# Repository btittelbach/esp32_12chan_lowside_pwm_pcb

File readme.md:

# esp32_12chan_lowside_pwm_pcb

Open Hardware PCB designed to drive 12 low-side PWM channels.

It's designed to work with e.g. WLED firmware and can drive up to 4 RGB LED strips.

You can however use it for whatever you want.
Free-wheeling diodes were added, in case someone wants to use it to drive bigger inductive loads.

[Schematic](renderings/pcb_esp32_wled_pwm_multichannel.pdf)

## Power

### Input

Power by USB for easy flashing.

Or power via screw-terminal: DC from 4V up to 28V.

#### optional Sound-Reactive Microphone Input

- I2S SD pin: gpio4
- I2S WS pin: gpio14
- I2S SCK pin: gpio13

### Output

The four screw terminals each group VDD as well as 4 GPIO controlled PWM-channels to GND.

- terminal 1: VDD, gpio16, gpio17, gpio18
- terminal 2: VDD, gpio19, gpio21, gpio22
- terminal 3: VDD, gpio23, gpio25, gpio26
- terminal 4: VDD, gpio27, gpio32, gpio33

## Firmware

for easy use, flash WLED-ESP32 and use web-interface to configure
4 "LEDS" as RGB-Strips with GPIO pins listed above.

## Manufacturing

the board was not designed to minimize costs, but for durability.

The folder `esp32_12chan_lowside_pwm_pcb_v3` includes all manufacturing files and information,
so you should easily be able to order your own.

See [fabrication_data.md](esp32_12chan_lowside_pwm_pcb_v3/fabrication_data.md) for specs often asked in order to get a quote.

### Expensive Parts
- the MosFETs
- the choosen ESP32, though you may choose a version with less Flash
- the QFN USB to UART bridge
- the buck regulator

### Costs

big price hike in 2025:

- per PCB the parts cost roughly 23 USD
- production+assembly+parts come to roughly 54 USD per PCB

## License

This project is licensed under the CERN OH License - see the [LICENSE](LICENSE.txt) file for details

## Photos

## Ordering

List of PCB Suppliers which one-click ordering for the board. (so far only one)

- [PCBWay](https://www.pcbway.com/project/shareproject/W18448ASS50_esp32_12chan_wled_pwm_v3_13ab729a.html)

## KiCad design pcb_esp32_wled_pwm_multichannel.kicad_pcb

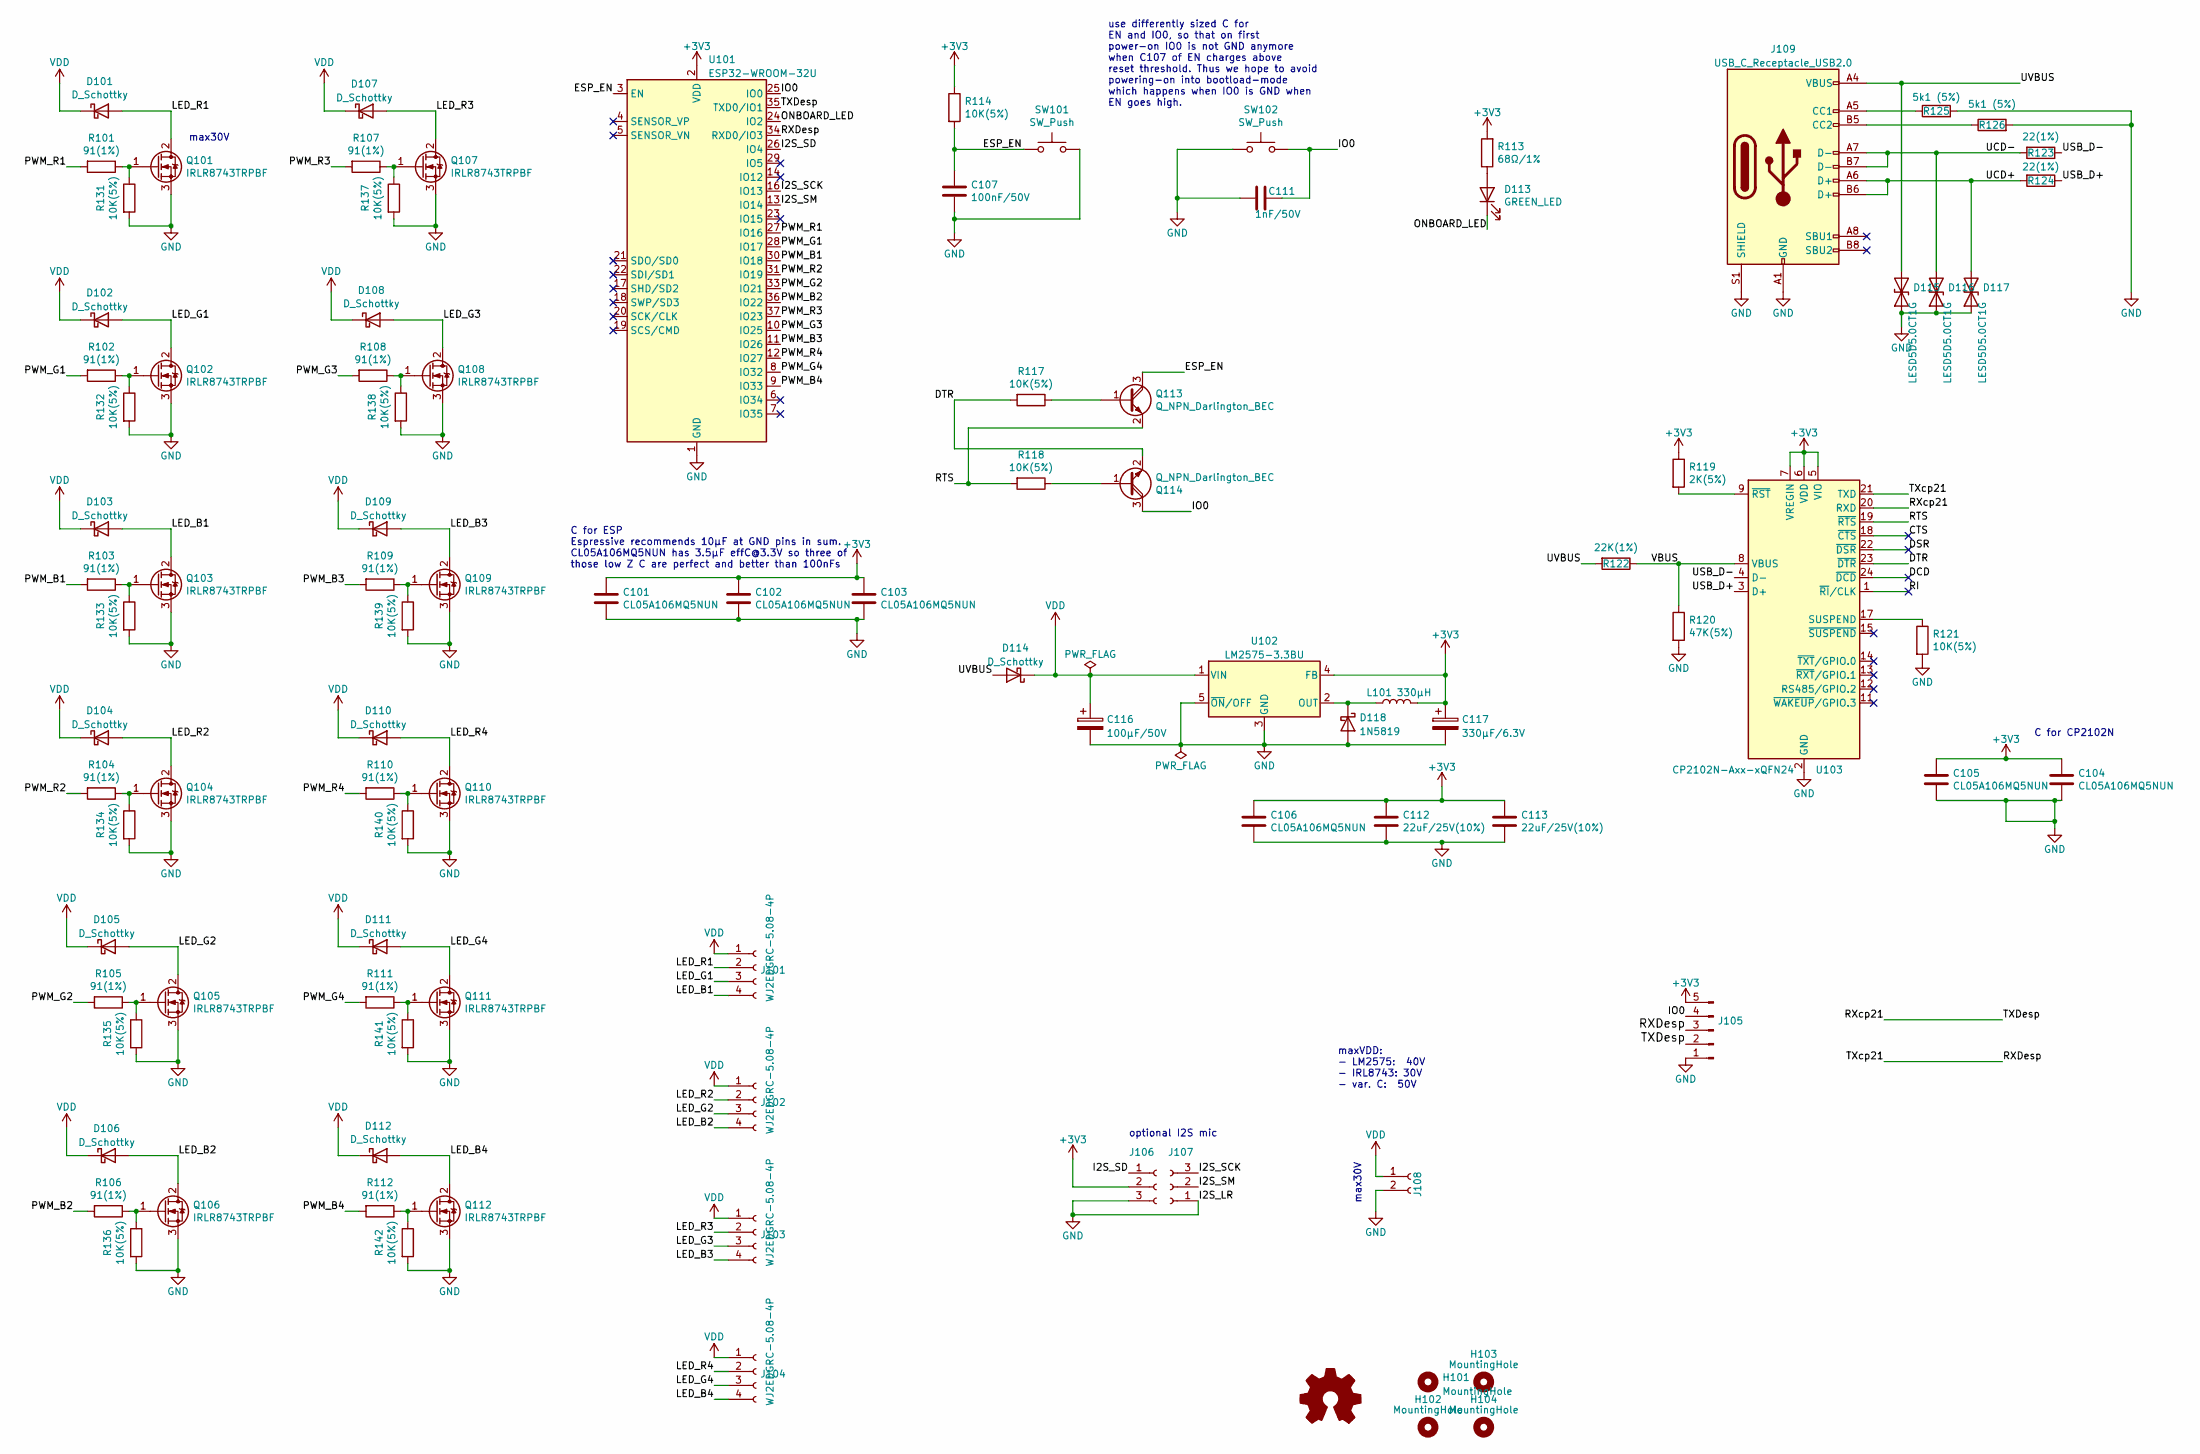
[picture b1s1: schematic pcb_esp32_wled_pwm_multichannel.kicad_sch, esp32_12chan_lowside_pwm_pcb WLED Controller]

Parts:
C101, C102, C103, C104, C105, C106: CL05A106MQ5NUN; C_0402_1005Metric; LCSC C15525
C107: 100nF/50V; C_0603_1608Metric; LCSC C42998
C111: 1nF/50V; C_0603_1608Metric; LCSC C100040
C112, C113: 22uF/25V(10%); C_1210_3225Metric; LCSC C337455
C116: 100µF/50V; CP_Elec_6.3x7.7; LCSC C311622
C117: 330µF/6.3V; CP_Elec_6.3x7.7; LCSC C74623
D101, D102, D103, D104, D105, D106, D107, D108, D109, D110, D111, D112, D114: D_Schottky; D_SOD-123F; LCSC C496544
D113: GREEN_LED; LED_0603_1608Metric; LCSC C89809
D115, D116, D117: LESD5D5.0CT1G; D_SOD-523; LCSC C383211
D118: 1N5819; D_DO-41_SOD81_P10.16mm_Horizontal
H101, H102, H103, H104: MountingHole; MountingHole_3.2mm_M3_ISO7380
J101, J102, J103, J104: WJ2EDGRC-5.08-4P; 2EDGRC-5.08-04P-14-100AH; LCSC C8446
J105: Conn_01x05_Male; PinHeader_1x05_P2.54mm_Vertical
J106, J107: Conn_01x03_Female; PinSocket_1x03_P2.54mm_Vertical; LCSC C358717
J108: Conn_01x02_Female; 2EDGRC-5.08-02P-14-100AH; LCSC C3697
J109: USB_C_Receptacle_USB2.0; USB_C_Receptacle_CIKI_TYPE-C-2.0-16PIN-SMT-3; LCSC C2987386
L101: 330µH; L_12x12mm_H8mm; LCSC C2929508
Q101, Q102, Q103, Q104, Q105, Q106, Q107, Q108, Q109, Q110, Q111, Q112: IRLR8743TRPBF; TO-252-2; LCSC C3040285
Q113, Q114: Q_NPN_Darlington_BEC; SOT-23; LCSC C164885
R101, R102, R103, R104, R105, R106, R107, R108, R109, R110, R111, R112: 91(1%); R_0603_1608Metric
R113: 68Ω/1%; R_0603_1608Metric; LCSC C126362
R114, R117, R118, R121, R131, R132, R133, R134, R135, R136, R137, R138, R139, R140, R141, R142: 10K(5%); R_0603_1608Metric
R119: 2K(5%); R_0603_1608Metric
R120: 47K(5%); R_0603_1608Metric
R122: 22K(1%); R_0603_1608Metric
R123, R124: 22(1%); R_0603_1608Metric
R125, R126: 5k1 (5%); R_0603_1608Metric
SW101, SW102: SW_Push; SW_SPST_B3SL-1022P; LCSC C86708
SYM101: Logo_Open_Hardware_Small; OSHW-Logo2_7.3x6mm_SilkScreen
U101: ESP32-WROOM-32U; LCSC C328062
U102: LM2575-3.3BU; TO-263-5_TabPin3; LCSC C70337
U103: CP2102N-Axx-xQFN24; QFN-24-1EP_4x4mm_P0.5mm_EP2.6x2.6mm; LCSC C969151

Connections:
+3V3: C101.1, C102.1, C103.1, C104.1, C105.1, C106.1, C112.1, C113.1, C117.1, J105.5, J106.2, L101.2, R113.2, R114.1, R119.1, U101.2 (VDD), U102.4 (FB), U103.5 (VIO), U103.6 (VDD), U103.7 (VREGIN)
/CTS: U103.18 (~CTS)
/DCD: U103.24 (~DCD)
/DSR: U103.22 (~DSR)
/DTR: Q114.2 (E), R117.2, U103.23 (~DTR)
/ESP_EN: C107.1, Q113.3 (C), R114.2, SW101.1, U101.3 (EN)
/I2S_SCK: J107.3, U101.16 (IO13)
/I2S_SD: J106.1, U101.26 (IO4)
/I2S_SM: J107.2, U101.13 (IO14)
/IO0: C111.1, J105.4, Q114.3 (C), SW102.2, U101.25 (IO0)
/LED_B1: D103.2 (A), J101.4, Q103.2 (D)
/LED_B2: D106.2 (A), J102.4, Q106.2 (D)
/LED_B3: D109.2 (A), J103.4, Q109.2 (D)
/LED_B4: D112.2 (A), J104.4, Q112.2 (D)
/LED_G1: D102.2 (A), J101.3, Q102.2 (D)
/LED_G2: D105.2 (A), J102.3, Q105.2 (D)
/LED_G3: D108.2 (A), J103.3, Q108.2 (D)
/LED_G4: D111.2 (A), J104.3, Q111.2 (D)
/LED_R1: D101.2 (A), J101.2, Q101.2 (D)
/LED_R2: D104.2 (A), J102.2, Q104.2 (D)
/LED_R3: D107.2 (A), J103.2, Q107.2 (D)
/LED_R4: D110.2 (A), J104.2, Q110.2 (D)
/ONBOARD_LED: D113.1 (K), U101.24 (IO2)
/PWM_B1: R103.2, U101.30 (IO18)
/PWM_B2: R106.2, U101.36 (IO22)
/PWM_B3: R109.2, U101.11 (IO26)
/PWM_B4: R112.2, U101.9 (IO33)
/PWM_G1: R102.2, U101.28 (IO17)
/PWM_G2: R105.2, U101.33 (IO21)
/PWM_G3: R108.2, U101.10 (IO25)
/PWM_G4: R111.2, U101.8 (IO32)
/PWM_R1: R101.2, U101.27 (IO16)
/PWM_R2: R104.2, U101.31 (IO19)
/PWM_R3: R107.2, U101.37 (IO23)
/PWM_R4: R110.2, U101.12 (IO27)
/RI: U103.1 (~RI/CLK)
/RTS: Q113.2 (E), R118.2, U103.19 (~RTS)
/RXDesp: J105.3, U101.34 (RXD0/IO3), U103.21 (TXD)
/RXcp21: J105.2, U101.35 (TXD0/IO1), U103.20 (RXD)
/UCD+: D117.2 (A2), J109.A6 (D+), J109.B6 (D+), R124.2
/UCD-: D116.2 (A2), J109.A7 (D-), J109.B7 (D-), R123.2
/USB_D+: R124.1, U103.3 (D+)
/USB_D-: R123.1, U103.4 (D-)
/UVBUS: D114.2 (A), D115.2 (A2), J109.A4 (VBUS), J109.A9 (VBUS), J109.B4 (VBUS), J109.B9 (VBUS), R122.2
/VBUS: R120.1, R122.1, U103.8 (VBUS)
GND: C101.2, C102.2, C103.2, C104.2, C105.2, C106.2, C107.2, C111.2, C112.2, C113.2, C116.2, C117.2, D115.1 (A1), D116.1 (A1), D117.1 (A1), D118.2 (A), J105.1, J106.3, J107.1, J108.2, J109.A1 (GND), J109.A12 (GND), J109.B1 (GND), J109.B12 (GND), J109.S1 (SHIELD), Q101.3 (S), Q102.3 (S), Q103.3 (S), Q104.3 (S), Q105.3 (S), Q106.3 (S), Q107.3 (S), Q108.3 (S), Q109.3 (S), Q110.3 (S), Q111.3 (S), Q112.3 (S), R120.2, R121.2, R125.2, R126.2, R131.2, R132.2, R133.2, R134.2, R135.2, R136.2, R137.2, R138.2, R139.2, R140.2, R141.2, R142.2, SW101.2, SW102.1, U101.1 (GND), U101.15 (GND), U101.38 (GND), U101.39 (GND), U102.3 (GND), U102.5 (~ON/OFF), U103.2 (GND), U103.25 (GND)
unnamed: D113.2 (A), R113.1
unnamed: D118.1 (K), L101.1, U102.2 (OUT)
unnamed: J109.A5 (CC1), R125.1
unnamed: J109.B5 (CC2), R126.1
unnamed: Q101.1 (G), R101.1, R131.1
unnamed: Q102.1 (G), R102.1, R132.1
unnamed: Q103.1 (G), R103.1, R133.1
unnamed: Q104.1 (G), R104.1, R134.1
unnamed: Q105.1 (G), R105.1, R135.1
unnamed: Q106.1 (G), R106.1, R136.1
unnamed: Q107.1 (G), R107.1, R137.1
unnamed: Q108.1 (G), R108.1, R138.1
unnamed: Q109.1 (G), R109.1, R139.1
unnamed: Q110.1 (G), R110.1, R140.1
unnamed: Q111.1 (G), R111.1, R141.1
unnamed: Q112.1 (G), R112.1, R142.1
unnamed: Q113.1 (B), R117.1
unnamed: Q114.1 (B), R118.1
unnamed: R121.1, U103.17 (SUSPEND)
unnamed: R119.2, U103.9 (~RST)
VDD: C116.1, D101.1 (K), D102.1 (K), D103.1 (K), D104.1 (K), D105.1 (K), D106.1 (K), D107.1 (K), D108.1 (K), D109.1 (K), D110.1 (K), D111.1 (K), D112.1 (K), D114.1 (K), J101.1, J102.1, J103.1, J104.1, J108.1, U102.1 (VIN)

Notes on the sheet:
use differently sized C for EN and IO0, so that on first power-on IO0 is not GND anymore when C107 of EN charges above reset threshold. Thus we hope to avoid powering-on into bootload-mode which happens when IO0 is GND when EN goes high.
maxVDD: - LM2575: 40V - IRL8743: 30V - var. C: 50V
C for ESP Espressive recommends 10μF at GND pins in sum. CL05A106MQ5NUN has 3.5μF effC@3.3V so three of those low Z C are perfect and better than 100nFs
optional I2S mic
max30V
C for CP2102N

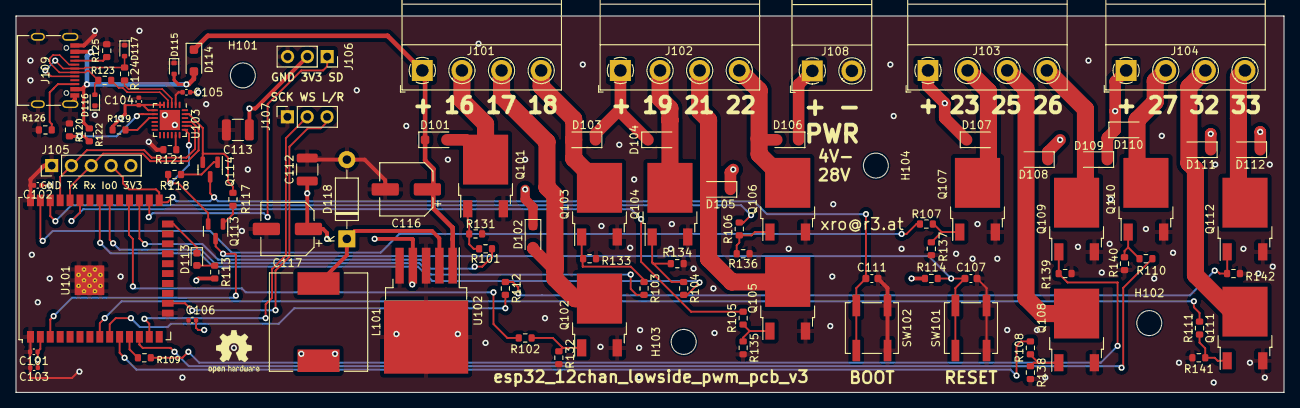
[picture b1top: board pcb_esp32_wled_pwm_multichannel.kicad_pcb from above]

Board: 4 copper layers, 162.6 x 48.3 mm, 100 parts (0 on the bottom side), 63 nets.

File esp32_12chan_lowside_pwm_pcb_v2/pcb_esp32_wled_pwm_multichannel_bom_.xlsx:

Description | Part | References | Value | Footprint | Quantity Per PCB | MF | MP | Distributor | LCSC | SMD | TH | Vf | If
Unpolarized capacitor | C | C102 C105 C107 C108 C109 C110 C111 C115 C118 | 100nF/50V | C_0603_1608Metric | 9 | FH | 0603F104M500NT | LCSC | C42998 | 1
Polarized capacitor | C_Polarized | C116 | 100µF/50V | CP_Elec_6.3x7.7 | 1 | Lelon | VZT101M1HTR-0607 | LCSC | C311622 | 1
Unpolarized capacitor | C | C104 | 10µF/25V | C_0805_2012Metric | 1 | FH | 0805X106K250NT | LCSC | C40894 | 1
Unpolarized capacitor | C | C103 | 1µF/50V | C_0603_1608Metric | 1 | Taiyo Yuden | UMK107AB7105KA-T | LCSC | C105174 | 1
Unpolarized capacitor | C | C101 | 220µF/6.3V(20%) | C_1206_3216Metric | 1 | Murata Electronics | GRM31CR60J227ME11L | LCSC | C412252 | 1
Unpolarized capacitor | C | C112 C113 | 22uF/25V(10%) | C_1210_3225Metric | 2 | Taiyo Yuden | TMK325B7226KM-TR | LCSC | C337455 | 1
Polarized capacitor | C_Polarized | C117 | 330µF/6.3V | CP_Elec_6.3x7.7 | 1 | RVT0J331M0607 | ROQANG | LCSC | C74623 | 1
Unpolarized capacitor | C | C114 | 4.7µF/6.3V(10%) | C_0603_1608Metric | 1 |  |  |  |  | 1
40V 1A Schottky Barrier Rectifier Diode, DO-41 | 1N5819 | D118 | 1N5819 | D_DO-41_SOD81_P10.16mm_Horizontal | 1 |  |  |  |  | 0 | 1
Schottky diode | D_Schottky | D101 D102 D103 D104 D105 D106 D107 D108 D109 D110 D111 D112 D114 | D_Schottky | D_SOD-123F | 13 | Shanghai Prisemi Elec | PSBD1DF40V2L | LCSC | C496544 | 1
Light emitting diode | LED | D113 | GREEN_LED | LED_0603_1608Metric | 1 | Foshan NationStar Optoelectronics | NCD0603C3 | LCSC | C89809 | 1 | 0 | 1.6V | 25mA
Bidirectional transient-voltage-suppression diode | D_TVS | D115 D116 D117 | LESD5D5.0CT1G | D_SOD-523 | 3 | LRC | LESD5D5.0CT1G | LCSC | C383211 | 1 | 0
Generic connector, single row, 01x02, script generated (kicad-library-utils/sch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 | Conn_01x02_Female | J108 | Conn_01x02_Female | 2EDGRC-5.08-02P-14-100AH | 1 | Ningbo Kangnex Elec | WJ2EDGRC-5.08-2P | LCSC | C3697 | 0 | 1
Generic connector, single row, 01x03, script generated (kicad-library-utils/sch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 | Conn_01x03_Female | J106 J107 | Conn_01x03_Female | PinSocket_1x03_P2.54mm_Vertical | 2 | generic | PinHeader,P=2.54mm,3Pin,1Row,1A | LCSC | C49257 | 0 | 1
USB 2.0-only Type-C Receptacle connector | USB_C_Receptacle_USB2.0 | J109 | USB_C_Receptacle_USB2.0 | USB_C_Receptacle_CIKI_TYPE-C-2.0-16PIN-SMT-3 | 1 | CIKI | TYPE-C-2.0-16PIN-SMT-3 | LCSC | C2987386 | 1 | 0
Generic connector, single row, 01x04, script generated (kicad-library-utils/sch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 | Conn_01x04_Female | J101 J102 J103 J104 | WJ2EDGRC-5.08-4P | 2EDGRC-5.08-04P-14-100AH | 4 | Ningbo Kangnex Elec | WJ2EDGRC-5.08-4P | LCSC | C8446 | 0 | 1
Inductor | L | L101 | 330µH | L_12x12mm_H8mm | 1 | SHOU HAN | CYH127-330UH | LCSC | C2929508 | 1
62A Id, 30V Vds, 8.7 mOhm Rds, N-Channel HEXFET Power MOSFET, TO-220 | IRLB8721PBF | Q101 Q102 Q103 Q104 Q105 Q106 Q107 Q108 Q109 Q110 Q111 Q112 | IRLR8743TRPBF | TO-252-2 | 12 | Infineon Technologies | IRLR8743TRPBF | LCSC | C3040285 | 1 | 0
NPN Darlington transistor, base/emitter/collector | Q_NPN_Darlington_BEC | Q113 Q114 | Q_NPN_Darlington_BEC | SOT-23 | 2 | JIANGSU CHANGJIANG ELECTRONICS | SS8050 | LCSC | C164885 | 1
Resistor | R | R114 R117 R118 R121 | 10K(5%) | R_0603_1608Metric | 4 |  |  |  |  | 1
Resistor | R | R123 R124 | 22(1%) | R_0603_1608Metric | 2 |  |  |  |  | 1
Resistor | R | R122 | 22K(1%) | R_0603_1608Metric | 1 |  |  |  |  | 1
Resistor | R | R119 | 2K(5%) | R_0603_1608Metric | 1 |  |  |  |  | 1 | 0
Resistor | R | R120 | 47K(5%) | R_0603_1608Metric | 1 |  |  |  |  | 1
Resistor | R | R125 R126 | 5k1 (5%) | R_0603_1608Metric | 2 |  |  |  |  | 1 | 0
Resistor | R | R113 | 68Ω/1% | R_0603_1608Metric | 1 | YAGEO | RC0603FR-0768RL | LCSC | C126362 | 1 | 0
Resistor | R | R101 R102 R103 R104 R105 R106 R107 R108 R109 R110 R111 R112 | 91(1%) | R_0603_1608Metric | 12 |  |  |  |  | 1
Push button switch, generic, two pins | SW_Push | SW101 SW102 | SW_Push | SW_SPST_B3SL-1022P | 2 | Omron Electronics | B3SL-1022P | LCSC | C86708 | 1
USB to UART master bridge, QFN-24 | CP2102N-Axx-xQFN24 | U103 | CP2102N-Axx-xQFN24 | QFN-24-1EP_4x4mm_P0.5mm_EP2.6x2.6mm | 1 | Silicon Labs | CP2102N-A02-GQFN24R | LCSC | C969151 | 1 | 0
RF Module, ESP32-D0WDQ6 SoC, Wi-Fi 802.11b/g/n, Bluetooth, BLE, 32-bit, 2.7-3.6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 | ESP32-WROOM-32 | U101 | ESP32-WROOM-32U | ESP32-WROOM-32U | 1 | Espressif | ESP32-WROOM-32U | LCSC | C328062 | 1
Fixed 3.3V 52kHz Simple 1A Buck Regulator, TO-263 | LM2575-3.3BU | U102 | LM2575-3.3BU | TO-263-5_TabPin3 | 1 | onsemi | LM2575D2T-3.3R4G | LCSC | C70337 | 1
 |  |  |  | 31 | 87 |  |  |  |  | 27 | 4
Number of unique Parts: | 31
Fitted Components: | 87
Number SMD Parts | 27
Number TH Parts | 4

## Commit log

2023-01-30 final cleaned v2 PCB
2023-01-30 Update readme.md
    img
2023-01-30 fab notes
2023-02-02 change footprint of polarized C to larger version that actually exists. Update BOM
2023-03-24 fix description of C117
2023-03-24 fabrication_info_markdown
2023-03-24 --typo
2023-03-24 costs
2023-03-24 fabrication
2023-03-25 microphone pins
2023-04-03 fix I2S microphone pin header. V3
2023-08-27 update future v3: reduce capacity of C111 debouncing BOOT0/IO0, so we are less likely to enter bootloader-mode on power-up
2023-08-27 label as v3 on silkscreen
2023-08-30 several fixes, thanks to mickdermack for reviewing
2023-09-07 wip: re-add 10ks discharge R to MosFETs
2023-09-07 mention option 2oz
2023-09-08 v3 release version: improved routing, closer C, WIP discharge-R done, new renderings, new gerber
2023-09-08 release v3
2024-04-19 license and photos
2024-09-11 PCB Enclosure v0.8
2024-09-11 update to kicad v8.0 format
2024-09-14 enclosure fixes
2024-09-15 enclosure: fix height
2024-09-15 enclosure: fix lid
2024-09-15 enclosure: recduce pcb tolerance offset
2024-09-15 enclosure: fix clips
2024-09-15 enclosure: make space for capacities
2024-09-15 enclosure: added slots for degson clips
2024-09-15 enclosure: remove old
2024-09-15 update renderings
2024-09-18 increase height tolerances. more space for th-pins. more space for optional microphone.
2024-09-18 fix clips and notches. Carve out corners for printers that tend to round in hard edges.
2024-09-18 enlosure: add pin labels
2024-09-19 enclosure: configure inscription depth
2024-09-30 re-export to 3mf
2024-10-01 enclosure variant
2025-01-08 fix one pdf link
2025-01-25 v3.1 change Cs
2025-05-13 USB-C plug replacement
2025-05-14 more precise fabrication notes
2025-05-14 prices and order link
2025-06-25 re-export BOM and remove KiCAD-symbol-description which confuses PCB supplier
